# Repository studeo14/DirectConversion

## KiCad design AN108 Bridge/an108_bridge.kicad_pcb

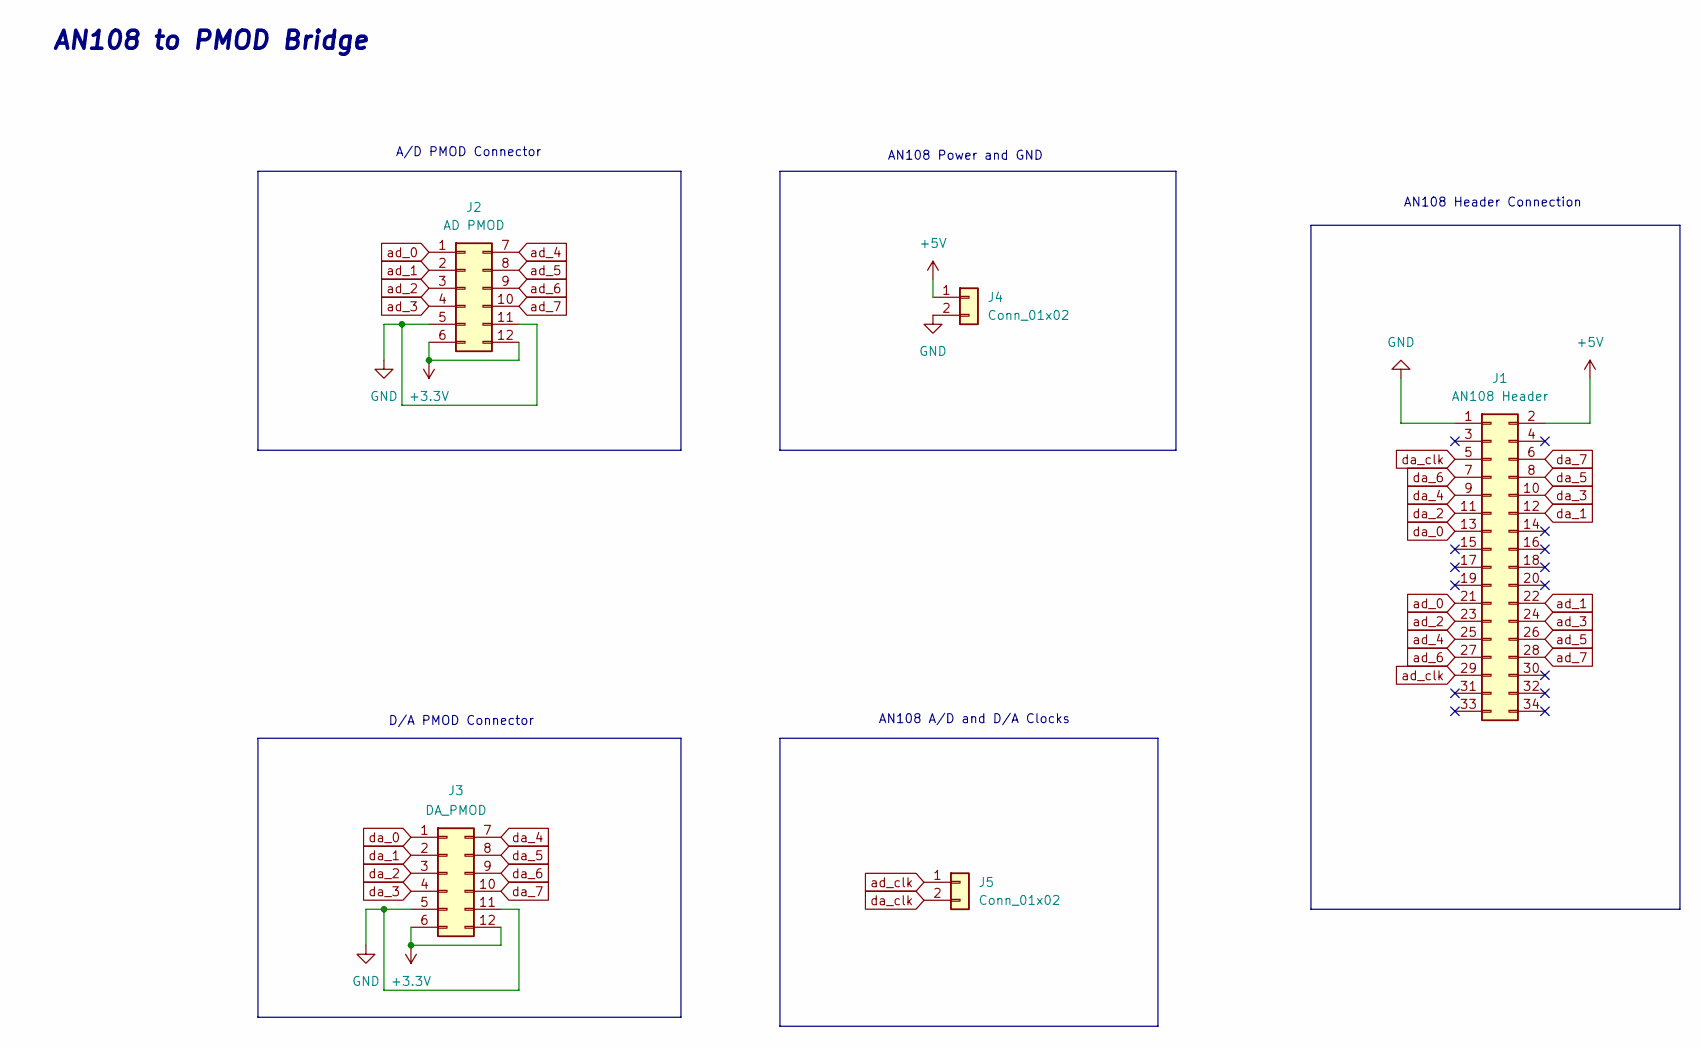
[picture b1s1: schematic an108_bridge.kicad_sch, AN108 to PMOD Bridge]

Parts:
J1: AN108 Header; PinHeader_2x17_P2.54mm_Vertical
J2: AD PMOD; pmod_pin_array_6x2
J3: DA_PMOD; pmod_pin_array_6x2
J4, J5: Conn_01x02; PinHeader_1x02_P2.54mm_Vertical

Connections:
+3.3V: J2.6, J2.12, J3.6, J3.12
+5V: J1.2, J4.1
GND: J1.1, J2.5, J2.11, J3.5, J3.11, J4.2
ad_0: J1.21, J2.1
ad_1: J1.22, J2.2
ad_2: J1.23, J2.3
ad_3: J1.24, J2.4
ad_4: J1.25, J2.7
ad_5: J1.26, J2.8
ad_6: J1.27, J2.9
ad_7: J1.28, J2.10
ad_clk: J1.29, J5.1
da_0: J1.13, J3.1
da_1: J1.12, J3.2
da_2: J1.11, J3.3
da_3: J1.10, J3.4
da_4: J1.9, J3.7
da_5: J1.8, J3.8
da_6: J1.7, J3.9
da_7: J1.6, J3.10
da_clk: J1.5, J5.2

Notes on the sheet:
AN108 to PMOD Bridge
AN108 A/D and D/A Clocks
D/A PMOD Connector
A/D PMOD Connector
AN108 Power and GND
AN108 Header Connection

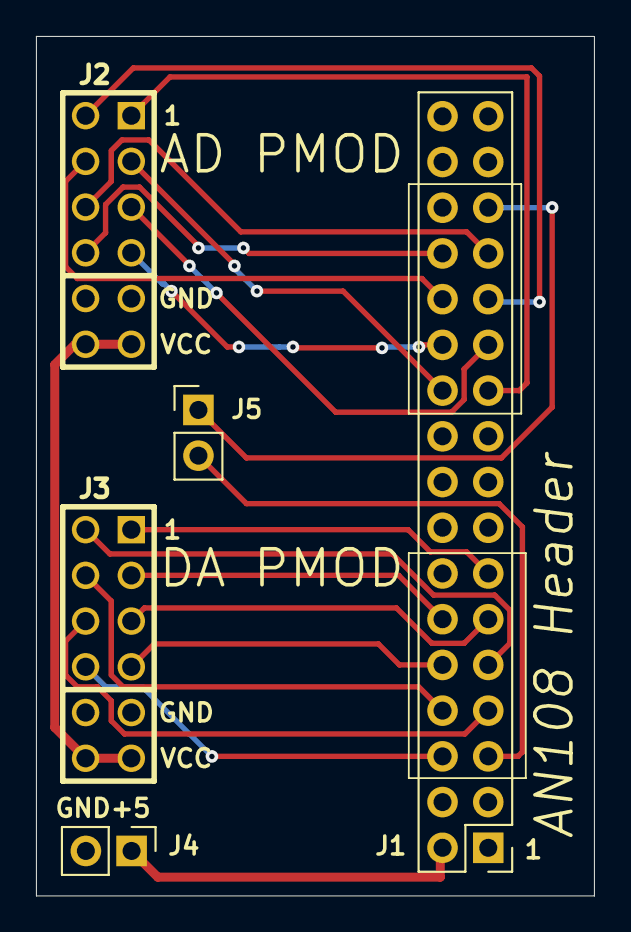
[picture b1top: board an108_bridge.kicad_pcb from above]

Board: 2 copper layers, 31.0 x 47.8 mm, 5 parts (0 on the bottom side), 21 nets.

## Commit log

2024-04-18 Initial
2024-05-15 Add AN108 Bridge KiCAD Files
2024-05-15 Move kicad files to seperate folder
2024-05-31 Swapped +5v and GND on AN108 header
2024-05-31 Passthrough design
2024-06-06 Transfer downconvertion design to top module.
    Added tooling configs, additional testing done.
